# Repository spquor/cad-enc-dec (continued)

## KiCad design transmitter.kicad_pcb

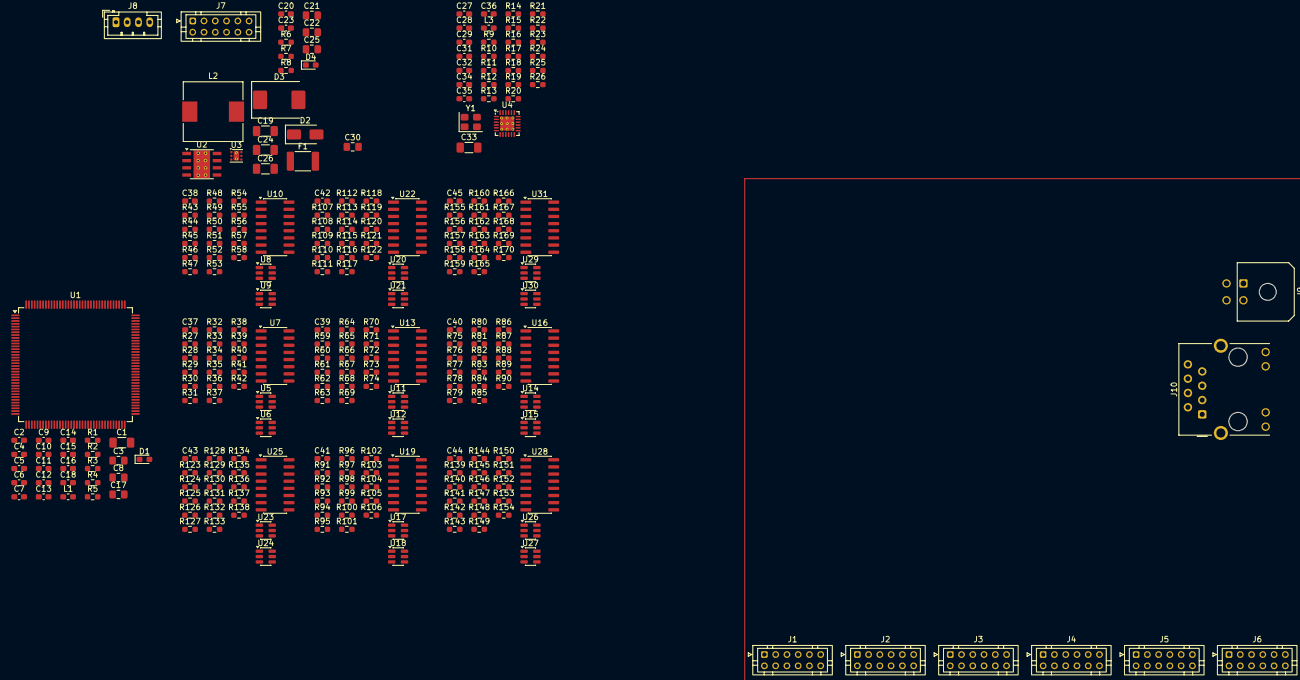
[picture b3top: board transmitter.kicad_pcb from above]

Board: 2 copper layers, 265 parts (0 on the bottom side), 264 nets, no tracks yet.

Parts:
C1, C19, C33: 10uF; C_1206_3216Metric_Pad1.33x1.80mm_HandSolder
C2, C4, C5, C6, C7, C9, C10, C11, C12, C13, C14, C15, C16, C18, C23, C29, C32, C34, C35, C36, C37, C38, C39, C40, C41, C42, C43, C44, C45: 100nF; C_0603_1608Metric_Pad1.08x0.95mm_HandSolder
C3, C8: 2.2uF; C_0805_2012Metric_Pad1.18x1.45mm_HandSolder
C17, C21, C22, C25, C30: 1uF; C_0805_2012Metric_Pad1.18x1.45mm_HandSolder
C20: 220nF; C_0603_1608Metric_Pad1.08x0.95mm_HandSolder
C24, C26: 22uF; C_1206_3216Metric_Pad1.33x1.80mm_HandSolder
C27, C28: 30pF; C_0603_1608Metric_Pad1.08x0.95mm_HandSolder
C31: 470pF; C_0603_1608Metric_Pad1.08x0.95mm_HandSolder
D1, D4: LED Blue; D_0603_1608Metric_Pad1.05x0.95mm_HandSolder
D2: SMAJ28A; D_SMA
D3: SS54; D_SMC
F1: Fuse 24V 3A; Fuse_1812_4532Metric_Pad1.30x3.40mm_HandSolder
J1, J2, J3, J4, J5, J6, J7: JST PHD B12B; JST_PHD_B12B-PHDSS_2x06_P2.00mm_Vertical
J8: JST PH B4B; JST_PH_B4B-PH-K_1x04_P2.00mm_Vertical
J9: Power MX 3.0; Molex_Micro-Fit_3.0_43045-0400_2x02_P3.00mm_Horizontal
J10: HR911105A; RJ45_Hanrun_HR911105A_Horizontal
L1, L3: 600R@100Mhz; L_0603_1608Metric_Pad1.05x0.95mm_HandSolder
L2: 2.2uH; L_10.4x10.4_H4.8
R1, R2, R3, R5, R6, R14, R15, R16, R17, R18, R24: 10K; R_0603_1608Metric_Pad0.98x0.95mm_HandSolder
R4, R39, R40, R41, R42, R55, R56, R57, R58, R71, R72, R73, R74, R87, R88, R89, R90, R103, R104, R105, R106, R119, R120, R121, R122, R135, R136, R137, R138, R151, R152, R153, R154, R167, R168, R169, R170: 0R; R_0603_1608Metric_Pad0.98x0.95mm_HandSolder
R7: 100K; R_0603_1608Metric_Pad0.98x0.95mm_HandSolder
R8: 24K9; R_0603_1608Metric_Pad0.98x0.95mm_HandSolder
R9, R10, R11, R12, R31, R32, R33, R34, R35, R36, R37, R38, R47, R48, R49, R50, R51, R52, R53, R54, R63, R64, R65, R66, R67, R68, R69, R70, R79, R80, R81, R82, R83, R84, R85, R86, R95, R96, R97, R98, R99, R100, R101, R102, R111, R112, R113, R114, R115, R116, R117, R118, R127, R128, R129, R130, R131, R132, R133, R134, R143, R144, R145, R146, R147, R148, R149, R150, R159, R160, R161, R162, R163, R164, R165, R166: 10; R_0603_1608Metric_Pad0.98x0.95mm_HandSolder
R13: 1K5; R_0603_1608Metric_Pad0.98x0.95mm_HandSolder
R19, R20, R21, R23: 49.9; R_0603_1608Metric_Pad0.98x0.95mm_HandSolder
R22: 12K1; R_0603_1608Metric_Pad0.98x0.95mm_HandSolder
R25, R26: 270; R_0603_1608Metric_Pad0.98x0.95mm_HandSolder
R27, R28, R29, R30, R43, R44, R45, R46, R59, R60, R61, R62, R75, R76, R77, R78, R91, R92, R93, R94, R107, R108, R109, R110, R123, R124, R125, R126, R139, R140, R141, R142, R155, R156, R157, R158: 100; R_0603_1608Metric_Pad0.98x0.95mm_HandSolder
U1: STM32H723ZGT; LQFP-144_20x20mm_P0.5mm
U2: LMR33630B; Texas_HSOP-8-1EP_3.9x4.9mm_P1.27mm_ThermalVias
U3: TLV76733; WSON-6-1EP_2x2mm_P0.65mm_EP1x1.6mm_ThermalVias
U4: LAN8742AI; VQFN-24-1EP_4x4mm_P0.5mm_EP2.5x2.5mm_ThermalVias
U5, U6, U8, U9, U11, U12, U14, U15, U17, U18, U20, U21, U23, U24, U26, U27, U29, U30: SRV05-4; SOT-23-6
U7, U10, U13, U16, U19, U22, U25, U28, U31: AM26LV32E; SOIC-16_3.9x9.9mm_P1.27mm
Y1: ABM8G-25MHz; Crystal_SMD_3225-4Pin_3.2x2.5mm

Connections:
+3V3: C1.1, C2.1, C4.1, C5.1, C6.1, C7.1, C9.1, C10.1, C11.1, C12.1, C13.1, C14.1, C15.1, C16.1, C25.1, C29.1, C37.2, C38.2, C39.2, C40.2, C41.2, C42.2, C43.2, C44.2, C45.2, D1.2 (A), J8.1, L1.2, L3.1, R2.1, R3.1, R5.1, R13.2, R14.2, R15.2, R16.2, R17.2, U1.6 (VBAT), U1.17 (VDD), U1.30 (VDD), U1.39 (VDD), U1.52 (VDD), U1.62 (VDD), U1.72 (VDD), U1.84 (VDD), U1.95 (VDD33USB), U1.108 (VDD), U1.121 (VDD), U1.131 (VDD), U1.144 (VDD), U3.1 (OUT), U3.2 (SNS), U4.9 (VDDIO), U7.4 (G), U7.16 (VDD), U10.4 (G), U10.16 (VDD), U13.4 (G), U13.16 (VDD), U16.4 (G), U16.16 (VDD), U19.4 (G), U19.16 (VDD), U22.4 (G), U22.16 (VDD), U25.4 (G), U25.16 (VDD), U28.4 (G), U28.16 (VDD), U31.4 (G), U31.16 (VDD)
+5V: C22.1, C24.1, C26.1, J7.1, J7.3, J7.5, J7.7, J7.9, J7.11, L2.2, R7.2, U3.4 (EN), U3.6 (IN)
+24V: C19.1, C20.1, D3.1 (K), D4.2 (A), F1.2, U2.2 (VIN), U2.3 (EN)
/EN1_A: R39.2, U1.15 (PF5)
/EN1_A1: J1.1, R27.1, R31.1, U5.1 (IO1)
/EN1_A2: J1.2, R27.2, R32.1, U5.3 (IO2)
/EN1_B: R40.2, U1.14 (PF4)
/EN1_B1: J1.3, R28.1, R33.1, U5.4 (IO3)
/EN1_B2: J1.4, R28.2, R34.1, U5.6 (IO4)
/EN1_U: R42.2, U1.12 (PF2)
/EN1_U1: J1.7, R30.1, R37.1, U6.4 (IO3)
/EN1_U2: J1.8, R30.2, R38.1, U6.6 (IO4)
/EN1_V: R55.2, U1.11 (PF1)
/EN1_V1: J1.9, R43.1, R47.1, U8.1 (IO1)
/EN1_V2: J1.10, R43.2, R48.1, U8.3 (IO2)
/EN1_W: R56.2, U1.10 (PF0)
/EN1_W1: J1.11, R44.1, R49.1, U8.4 (IO3)
/EN1_W2: J1.12, R44.2, R50.1, U8.6 (IO4)
/EN1_Z: R41.2, U1.13 (PF3)
/EN1_Z1: J1.5, R29.1, R35.1, U6.1 (IO1)
/EN1_Z2: J1.6, R29.2, R36.1, U6.3 (IO2)
/EN2_A: R57.2, U1.59 (PE8)
/EN2_A1: J2.1, R45.1, R51.1, U9.1 (IO1)
/EN2_A2: J2.2, R45.2, R52.1, U9.3 (IO2)
/EN2_B: R58.2, U1.63 (PE10)
/EN2_B1: J2.3, R46.1, R53.1, U9.4 (IO3)
/EN2_B2: J2.4, R46.2, R54.1, U9.6 (IO4)
/EN2_U: R72.2, U1.66 (PE13)
/EN2_U1: J2.7, R60.1, R65.1, U11.4 (IO3)
/EN2_U2: J2.8, R60.2, R66.1, U11.6 (IO4)
/EN2_V: R73.2, U1.60 (PE9)
/EN2_V1: J2.9, R61.1, R67.1, U12.1 (IO1)
/EN2_V2: J2.10, R61.2, R68.1, U12.3 (IO2)
/EN2_W: R74.2, U1.64 (PE11)
/EN2_W1: J2.11, R62.1, R69.1, U12.4 (IO3)
/EN2_W2: J2.12, R62.2, R70.1, U12.6 (IO4)
/EN2_Z: R71.2, U1.65 (PE12)
/EN2_Z1: J2.5, R59.1, R63.1, U11.1 (IO1)
/EN2_Z2: J2.6, R59.2, R64.1, U11.3 (IO2)
/EN3_A: R87.2, U1.77 (PD8)
/EN3_A1: J3.1, R75.1, R79.1, U14.1 (IO1)
/EN3_A2: J3.2, R75.2, R80.1, U14.3 (IO2)
/EN3_B: R88.2, U1.78 (PD9)
/EN3_B1: J3.3, R76.1, R81.1, U14.4 (IO3)
/EN3_B2: J3.4, R76.2, R82.1, U14.6 (IO4)
/EN3_U: R90.2, U1.80 (PD11)
/EN3_U1: J3.7, R78.1, R85.1, U15.4 (IO3)
/EN3_U2: J3.8, R78.2, R86.1, U15.6 (IO4)
/EN3_V: R103.2, U1.81 (PD12)
/EN3_V1: J3.9, R91.1, R95.1, U17.1 (IO1)
/EN3_V2: J3.10, R91.2, R96.1, U17.3 (IO2)
/EN3_W: R104.2, U1.82 (PD13)
/EN3_W1: J3.11, R92.1, R97.1, U17.4 (IO3)
/EN3_W2: J3.12, R92.2, R98.1, U17.6 (IO4)
/EN3_Z: R89.2, U1.79 (PD10)
/EN3_Z1: J3.5, R77.1, R83.1, U15.1 (IO1)
/EN3_Z2: J3.6, R77.2, R84.1, U15.3 (IO2)
/EN4_A: R105.2, U1.90 (PG5)
/EN4_A1: J4.1, R93.1, R99.1, U18.1 (IO1)
/EN4_A2: J4.2, R93.2, R100.1, U18.3 (IO2)
/EN4_B: R106.2, U1.91 (PG6)
/EN4_B1: J4.3, R94.1, R101.1, U18.4 (IO3)
/EN4_B2: J4.4, R94.2, R102.1, U18.6 (IO4)
/EN4_U: R120.2, U1.93 (PG8)
/EN4_U1: J4.7, R108.1, R113.1, U20.4 (IO3)
/EN4_U2: J4.8, R108.2, R114.1, U20.6 (IO4)
/EN4_V: R121.2, U1.96 (PC6)
/EN4_V1: J4.9, R109.1, R115.1, U21.1 (IO1)
/EN4_V2: J4.10, R109.2, R116.1, U21.3 (IO2)
/EN4_W: R122.2, U1.97 (PC7)
/EN4_W1: J4.11, R110.1, R117.1, U21.4 (IO3)
/EN4_W2: J4.12, R110.2, R118.1, U21.6 (IO4)
/EN4_Z: R119.2, U1.92 (PG7)
/EN4_Z1: J4.5, R107.1, R111.1, U20.1 (IO1)
/EN4_Z2: J4.6, R107.2, R112.1, U20.3 (IO2)
/EN5_A: R135.2, U1.111 (PC10)
/EN5_A1: J5.1, R123.1, R127.1, U23.1 (IO1)
/EN5_A2: J5.2, R123.2, R128.1, U23.3 (IO2)
/EN5_B: R136.2, U1.112 (PC11)
/EN5_B1: J5.3, R124.1, R129.1, U23.4 (IO3)
/EN5_B2: J5.4, R124.2, R130.1, U23.6 (IO4)
/EN5_U: R138.2, U1.115 (PD1)
/EN5_U1: J5.7, R126.1, R133.1, U24.4 (IO3)
/EN5_U2: J5.8, R126.2, R134.1, U24.6 (IO4)
/EN5_V: R151.2, U1.110 (PA15(JTDI))
/EN5_V1: J5.9, R139.1, R143.1, U26.1 (IO1)
/EN5_V2: J5.10, R139.2, R144.1, U26.3 (IO2)
/EN5_W: R152.2, U1.133 (PB3(JTDO)
/EN5_W1: J5.11, R140.1, R145.1, U26.4 (IO3)
/EN5_W2: J5.12, R140.2, R146.1, U26.6 (IO4)
/EN5_Z: R137.2, U1.114 (PD0)
/EN5_Z1: J5.5, R125.1, R131.1, U24.1 (IO1)
/EN5_Z2: J5.6, R125.2, R132.1, U24.3 (IO2)
/EN6_A: R153.2, U1.125 (PG10)
/EN6_A1: J6.1, R141.1, R147.1, U27.1 (IO1)
/EN6_A2: J6.2, R141.2, R148.1, U27.3 (IO2)
/EN6_B: R154.2, U1.126 (PG11)
/EN6_B1: J6.3, R142.1, R149.1, U27.4 (IO3)
/EN6_B2: J6.4, R142.2, R150.1, U27.6 (IO4)
/EN6_U: R168.2, U1.128 (PG13)
/EN6_U1: J6.7, R156.1, R161.1, U29.4 (IO3)
/EN6_U2: J6.8, R156.2, R162.1, U29.6 (IO4)
/EN6_V: R169.2, U1.134 (PB4(NJTRST))
/EN6_V1: J6.9, R157.1, R163.1, U30.1 (IO1)
/EN6_V2: J6.10, R157.2, R164.1, U30.3 (IO2)
/EN6_W: R170.2, U1.135 (PB5)
/EN6_W1: J6.11, R158.1, R165.1, U30.4 (IO3)
/EN6_W2: J6.12, R158.2, R166.1, U30.6 (IO4)
/EN6_Z: R167.2, U1.127 (PG12)
/EN6_Z1: J6.5, R155.1, R159.1, U29.1 (IO1)
/EN6_Z2: J6.6, R155.2, R160.1, U29.3 (IO2)
/Ethernet/CRS: R11.1, U1.43 (PA7)
/Ethernet/MDC: R16.1, U1.27 (PC1), U4.13 (MDC)
/Ethernet/MDIO: R13.1, U1.36 (PA2), U4.12 (MDIO)
/Ethernet/REFCLK: R12.1, U1.35 (PA1)
/Ethernet/RXD0: R9.1, U1.44 (PC4)
/Ethernet/RXD1: R10.1, U1.45 (PC5)
/Ethernet/TXD0: U1.73 (PB12), U4.17 (TXD0)
/Ethernet/TXD1: U1.74 (PB13), U4.18 (TXD1)
/Ethernet/TXEN: U1.70 (PB11), U4.16 (TXEN)
/Ethernet/nRST: U1.69 (PB10), U4.15 (~RST)
/SWDCLK: J8.2, U1.109 (PA14(JTCK)
/SWDIO: J8.3, U1.105 (PA13(JTMS)
GND: C1.2, C2.2, C3.2, C4.2, C5.2, C6.2, C7.2, C8.2, C9.2, C10.2, C11.2, C12.2, C13.2, C14.2, C15.2, C16.2, C17.2, C18.2, C19.2, C20.2, C21.2, C22.2, C24.2, C25.2, C26.2, C27.1, C28.1, C29.2, C30.2, C31.2, C32.2, C33.2, C34.2, C35.2, C36.2, C37.1, C38.1, C39.1, C40.1, C41.1, C42.1, C43.1, C44.1, C45.1, D2.2 (A2), D3.2 (A), J7.2, J7.4, J7.6, J7.8, J7.10, J7.12, J8.4, J9.3, J9.4, J10.8, J10.SH, R1.1, R6.1, R8.1, R18.1, R22.1, R24.1, R25.1, R26.1, U1.16 (VSS), U1.31 (VSSA), U1.38 (VSS), U1.51 (VSS), U1.61 (VSS), U1.83 (VSS), U1.94 (VSS), U1.107 (VSS), U1.120 (VSS), U1.130 (VSS), U2.1 (GND), U2.9 (GND), U3.3 (GND), U3.5 (GND), U3.7 (PAD), U4.25 (VSS), U5.2 (VN), U6.2 (VN), U7.8 (GND), U7.12 (~G), U8.2 (VN), U9.2 (VN), U10.8 (GND), U10.12 (~G), U11.2 (VN), U12.2 (VN), U13.8 (GND), U13.12 (~G), U14.2 (VN), U15.2 (VN), U16.8 (GND), U16.12 (~G), U17.2 (VN), U18.2 (VN), U19.8 (GND), U19.12 (~G), U20.2 (VN), U21.2 (VN), U22.8 (GND), U22.12 (~G), U23.2 (VN), U24.2 (VN), U25.8 (GND), U25.12 (~G), U26.2 (VN), U27.2 (VN), U28.8 (GND), U28.12 (~G), U29.2 (VN), U30.2 (VN), U31.8 (GND), U31.12 (~G), Y1.2 (G), Y1.4 (G)
unnamed: C3.1, U1.71 (VCAP)
unnamed: C8.1, U1.106 (VCAP)
unnamed: D1.1 (K), R1.2
unnamed: D4.1 (K), R6.2
unnamed: J10.10, R25.2
unnamed: J10.11, R26.2
unnamed: C32.1, C33.1, C34.1, C35.1, C36.1, J10.4 (TCT), J10.5 (RCT), L3.2, R19.2, R20.2, R21.2, R23.2, U4.1 (VDD2A), U4.19 (VDD1A)
unnamed: J10.3 (RD+), R21.1, U4.23 (RXP)
unnamed: J10.6 (RD-), R23.1, U4.22 (RXN)
unnamed: J10.1 (TD+), R19.1, U4.21 (TXP)
unnamed: J10.2 (TD-), R20.1, U4.20 (TXN)
unnamed: R3.2, U1.138 (BOOT0)
unnamed: R2.2, U1.25 (NRST)
unnamed: R5.2, U1.143 (PDR_ON)
unnamed: C17.1, C18.1, L1.1, U1.33 (VDDA)
unnamed: R4.2, U1.32 (VREF+)
unnamed: C23.1, U2.7 (BOOT)
unnamed: R7.1, R8.2, U2.5 (FB)
unnamed: C23.2, L2.1, U2.8 (SW)
unnamed: C21.1, U2.6 (VCC)
unnamed: R11.2, U4.11 (CRS_DV/MODE2)
unnamed: J10.12, U4.3 (LED1/REGOFF)
unnamed: J10.9, R24.2, U4.2 (LED2/~INTSEL)
unnamed: R22.2, U4.24 (RBIAS)
unnamed: R9.2, R14.1, U4.8 (RXD0/MODE0)
unnamed: R10.2, R15.1, U4.7 (RXD1/MODE1)
unnamed: R18.2, U4.10 (RXER/PHYAD0)
unnamed: C30.1, C31.1, U4.6 (VDDCR)
unnamed: C27.2, U4.5 (XTAL1/CLKIN), Y1.3
unnamed: C28.2, U4.4 (XTAL2), Y1.1
unnamed: R12.2, R17.1, U4.14 (~INT/REFCLKO)
unnamed: R31.2, U7.2 (1A)
unnamed: R32.2, U7.1 (1B)
unnamed: R39.1, U7.3 (1Y)
unnamed: R33.2, U7.6 (2A)
unnamed: R34.2, U7.7 (2B)
unnamed: R40.1, U7.5 (2Y)
unnamed: R35.2, U7.10 (3A)
unnamed: R36.2, U7.9 (3B)
unnamed: R41.1, U7.11 (3Y)
unnamed: R37.2, U7.14 (4A)
unnamed: R38.2, U7.15 (4B)
unnamed: R42.1, U7.13 (4Y)
unnamed: R47.2, U10.2 (1A)
unnamed: R48.2, U10.1 (1B)
unnamed: R55.1, U10.3 (1Y)
unnamed: R49.2, U10.6 (2A)
unnamed: R50.2, U10.7 (2B)
unnamed: R56.1, U10.5 (2Y)
unnamed: R51.2, U10.10 (3A)
unnamed: R52.2, U10.9 (3B)
unnamed: R57.1, U10.11 (3Y)
unnamed: R53.2, U10.14 (4A)
unnamed: R54.2, U10.15 (4B)
unnamed: R58.1, U10.13 (4Y)
unnamed: R63.2, U13.2 (1A)
unnamed: R64.2, U13.1 (1B)
unnamed: R71.1, U13.3 (1Y)
unnamed: R65.2, U13.6 (2A)
unnamed: R66.2, U13.7 (2B)
unnamed: R72.1, U13.5 (2Y)
unnamed: R67.2, U13.10 (3A)
unnamed: R68.2, U13.9 (3B)
unnamed: R73.1, U13.11 (3Y)
unnamed: R69.2, U13.14 (4A)
unnamed: R70.2, U13.15 (4B)
unnamed: R74.1, U13.13 (4Y)
unnamed: R79.2, U16.2 (1A)
unnamed: R80.2, U16.1 (1B)
unnamed: R87.1, U16.3 (1Y)
unnamed: R81.2, U16.6 (2A)
unnamed: R82.2, U16.7 (2B)
unnamed: R88.1, U16.5 (2Y)
unnamed: R83.2, U16.10 (3A)
unnamed: R84.2, U16.9 (3B)
unnamed: R89.1, U16.11 (3Y)
unnamed: R85.2, U16.14 (4A)
unnamed: R86.2, U16.15 (4B)
unnamed: R90.1, U16.13 (4Y)
unnamed: R95.2, U19.2 (1A)
unnamed: R96.2, U19.1 (1B)
unnamed: R103.1, U19.3 (1Y)
unnamed: R97.2, U19.6 (2A)
unnamed: R98.2, U19.7 (2B)
unnamed: R104.1, U19.5 (2Y)
unnamed: R99.2, U19.10 (3A)
unnamed: R100.2, U19.9 (3B)
unnamed: R105.1, U19.11 (3Y)
unnamed: R101.2, U19.14 (4A)
unnamed: R102.2, U19.15 (4B)
unnamed: R106.1, U19.13 (4Y)
unnamed: R111.2, U22.2 (1A)
unnamed: R112.2, U22.1 (1B)
unnamed: R119.1, U22.3 (1Y)
unnamed: R113.2, U22.6 (2A)
unnamed: R114.2, U22.7 (2B)
unnamed: R120.1, U22.5 (2Y)
unnamed: R115.2, U22.10 (3A)
unnamed: R116.2, U22.9 (3B)
unnamed: R121.1, U22.11 (3Y)
unnamed: R117.2, U22.14 (4A)
unnamed: R118.2, U22.15 (4B)
unnamed: R122.1, U22.13 (4Y)
unnamed: R127.2, U25.2 (1A)
unnamed: R128.2, U25.1 (1B)
unnamed: R135.1, U25.3 (1Y)
unnamed: R129.2, U25.6 (2A)
unnamed: R130.2, U25.7 (2B)
unnamed: R136.1, U25.5 (2Y)
unnamed: R131.2, U25.10 (3A)
unnamed: R132.2, U25.9 (3B)
unnamed: R137.1, U25.11 (3Y)
unnamed: R133.2, U25.14 (4A)
unnamed: R134.2, U25.15 (4B)
unnamed: R138.1, U25.13 (4Y)
unnamed: R143.2, U28.2 (1A)
unnamed: R144.2, U28.1 (1B)
unnamed: R151.1, U28.3 (1Y)
unnamed: R145.2, U28.6 (2A)
unnamed: R146.2, U28.7 (2B)
unnamed: R152.1, U28.5 (2Y)
unnamed: R147.2, U28.10 (3A)
unnamed: R148.2, U28.9 (3B)
unnamed: R153.1, U28.11 (3Y)
unnamed: R149.2, U28.14 (4A)
unnamed: R150.2, U28.15 (4B)
unnamed: R154.1, U28.13 (4Y)
unnamed: R159.2, U31.2 (1A)
unnamed: R160.2, U31.1 (1B)
unnamed: R167.1, U31.3 (1Y)
unnamed: R161.2, U31.6 (2A)
unnamed: R162.2, U31.7 (2B)
unnamed: R168.1, U31.5 (2Y)
unnamed: R163.2, U31.10 (3A)
unnamed: R164.2, U31.9 (3B)
unnamed: R169.1, U31.11 (3Y)
unnamed: R165.2, U31.14 (4A)
unnamed: R166.2, U31.15 (4B)
unnamed: R170.1, U31.13 (4Y)
VDD: D2.1 (A1), F1.1, J9.1, J9.2

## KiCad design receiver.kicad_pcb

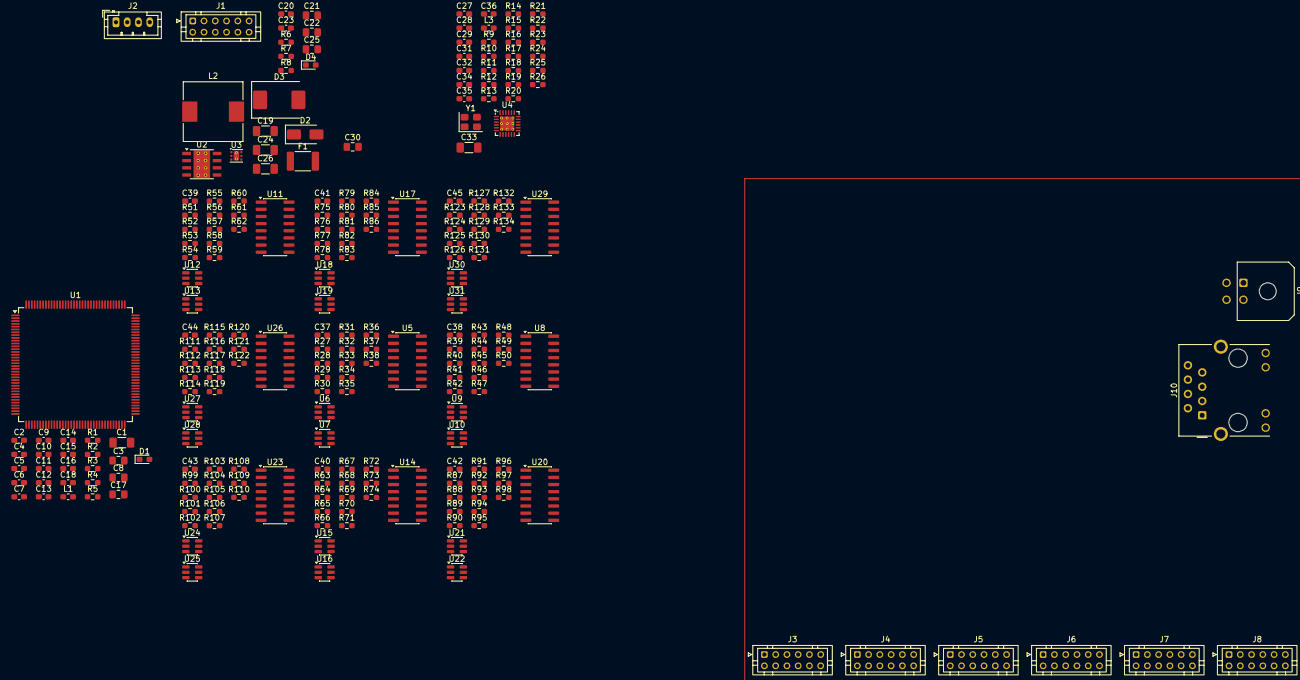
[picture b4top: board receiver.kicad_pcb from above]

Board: 2 copper layers, 229 parts (0 on the bottom side), 264 nets, no tracks yet.

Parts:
C1, C19, C33: 10uF; C_1206_3216Metric_Pad1.33x1.80mm_HandSolder
C2, C4, C5, C6, C7, C9, C10, C11, C12, C13, C14, C15, C16, C18, C23, C29, C32, C34, C35, C36, C37, C38, C39, C40, C41, C42, C43, C44, C45: 100nF; C_0603_1608Metric_Pad1.08x0.95mm_HandSolder
C3, C8: 2.2uF; C_0805_2012Metric_Pad1.18x1.45mm_HandSolder
C17, C21, C22, C25, C30: 1uF; C_0805_2012Metric_Pad1.18x1.45mm_HandSolder
C20: 220nF; C_0603_1608Metric_Pad1.08x0.95mm_HandSolder
C24, C26: 22uF; C_1206_3216Metric_Pad1.33x1.80mm_HandSolder
C27, C28: 30pF; C_0603_1608Metric_Pad1.08x0.95mm_HandSolder
C31: 470pF; C_0603_1608Metric_Pad1.08x0.95mm_HandSolder
D1, D4: LED Blue; D_0603_1608Metric_Pad1.05x0.95mm_HandSolder
D2: SMAJ28A; D_SMA
D3: SS54; D_SMC
F1: Fuse 24V 3A; Fuse_1812_4532Metric_Pad1.30x3.40mm_HandSolder
J1, J3, J4, J5, J6, J7, J8: JST PHD B12B; JST_PHD_B12B-PHDSS_2x06_P2.00mm_Vertical
J2: JST PH B4B; JST_PH_B4B-PH-K_1x04_P2.00mm_Vertical
J9: Power MX 3.0; Molex_Micro-Fit_3.0_43045-0400_2x02_P3.00mm_Horizontal
J10: HR911105A; RJ45_Hanrun_HR911105A_Horizontal
L1, L3: 600R@100Mhz; L_0603_1608Metric_Pad1.05x0.95mm_HandSolder
L2: 2.2uH; L_10.4x10.4_H4.8
R1, R2, R3, R5, R6, R14, R15, R16, R17, R18, R24: 10K; R_0603_1608Metric_Pad0.98x0.95mm_HandSolder
R4, R27, R28, R29, R30, R39, R40, R41, R42, R51, R52, R53, R54, R63, R64, R65, R66, R75, R76, R77, R78, R87, R88, R89, R90, R99, R100, R101, R102, R111, R112, R113, R114, R123, R124, R125, R126: 0R; R_0603_1608Metric_Pad0.98x0.95mm_HandSolder
R7: 100K; R_0603_1608Metric_Pad0.98x0.95mm_HandSolder
R8: 24K9; R_0603_1608Metric_Pad0.98x0.95mm_HandSolder
R9, R10, R11, R12, R31, R32, R33, R34, R35, R36, R37, R38, R43, R44, R45, R46, R47, R48, R49, R50, R55, R56, R57, R58, R59, R60, R61, R62, R67, R68, R69, R70, R71, R72, R73, R74, R79, R80, R81, R82, R83, R84, R85, R86, R91, R92, R93, R94, R95, R96, R97, R98, R103, R104, R105, R106, R107, R108, R109, R110, R115, R116, R117, R118, R119, R120, R121, R122, R127, R128, R129, R130, R131, R132, R133, R134: 10; R_0603_1608Metric_Pad0.98x0.95mm_HandSolder
R13: 1K5; R_0603_1608Metric_Pad0.98x0.95mm_HandSolder
R19, R20, R21, R23: 49.9; R_0603_1608Metric_Pad0.98x0.95mm_HandSolder
R22: 12K1; R_0603_1608Metric_Pad0.98x0.95mm_HandSolder
R25, R26: 270; R_0603_1608Metric_Pad0.98x0.95mm_HandSolder
U1: STM32H723ZGT; LQFP-144_20x20mm_P0.5mm
U2: LMR33630B; Texas_HSOP-8-1EP_3.9x4.9mm_P1.27mm_ThermalVias
U3: TLV76733; WSON-6-1EP_2x2mm_P0.65mm_EP1x1.6mm_ThermalVias
U4: LAN8742AI; VQFN-24-1EP_4x4mm_P0.5mm_EP2.5x2.5mm_ThermalVias
U5, U8, U11, U14, U17, U20, U23, U26, U29: AM26LV31E; SOIC-16_3.9x9.9mm_P1.27mm
U6, U7, U9, U10, U12, U13, U15, U16, U18, U19, U21, U22, U24, U25, U27, U28, U30, U31: SRV05-4; SOT-23-6
Y1: ABM8G-25MHz; Crystal_SMD_3225-4Pin_3.2x2.5mm

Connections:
+3V3: C1.1, C2.1, C4.1, C5.1, C6.1, C7.1, C9.1, C10.1, C11.1, C12.1, C13.1, C14.1, C15.1, C16.1, C25.1, C29.1, C37.2, C38.2, C39.2, C40.2, C41.2, C42.2, C43.2, C44.2, C45.2, D1.2 (A), J2.1, L1.2, L3.1, R2.1, R3.1, R5.1, R13.2, R14.2, R15.2, R16.2, R17.2, U1.6 (VBAT), U1.17 (VDD), U1.30 (VDD), U1.39 (VDD), U1.52 (VDD), U1.62 (VDD), U1.72 (VDD), U1.84 (VDD), U1.95 (VDD33USB), U1.108 (VDD), U1.121 (VDD), U1.131 (VDD), U1.144 (VDD), U3.1 (OUT), U3.2 (SNS), U4.9 (VDDIO), U5.4 (G), U5.16 (VDD), U8.4 (G), U8.16 (VDD), U11.4 (G), U11.16 (VDD), U14.4 (G), U14.16 (VDD), U17.4 (G), U17.16 (VDD), U20.4 (G), U20.16 (VDD), U23.4 (G), U23.16 (VDD), U26.4 (G), U26.16 (VDD), U29.4 (G), U29.16 (VDD)
+5V: C22.1, C24.1, C26.1, J1.1, J1.3, J1.5, J1.7, J1.9, J1.11, L2.2, R7.2, U3.4 (EN), U3.6 (IN)
+24V: C19.1, C20.1, D3.1 (K), D4.2 (A), F1.2, U2.2 (VIN), U2.3 (EN)
/EN1_A: R27.1, U1.15 (PF5)
/EN1_A1: J3.1, R31.2, U6.1 (IO1)
/EN1_A2: J3.2, R32.2, U6.3 (IO2)
/EN1_B: R28.1, U1.14 (PF4)
/EN1_B1: J3.3, R33.2, U6.4 (IO3)
/EN1_B2: J3.4, R34.2, U6.6 (IO4)
/EN1_U: R30.1, U1.12 (PF2)
/EN1_U1: J3.7, R37.2, U7.4 (IO3)
/EN1_U2: J3.8, R38.2, U7.6 (IO4)
/EN1_V: R39.1, U1.11 (PF1)
/EN1_V1: J3.9, R43.2, U9.1 (IO1)
/EN1_V2: J3.10, R44.2, U9.3 (IO2)
/EN1_W: R40.1, U1.10 (PF0)
/EN1_W1: J3.11, R45.2, U9.4 (IO3)
/EN1_W2: J3.12, R46.2, U9.6 (IO4)
/EN1_Z: R29.1, U1.13 (PF3)
/EN1_Z1: J3.5, R35.2, U7.1 (IO1)
/EN1_Z2: J3.6, R36.2, U7.3 (IO2)
/EN2_A: R41.1, U1.59 (PE8)
/EN2_A1: J4.1, R47.2, U10.1 (IO1)
/EN2_A2: J4.2, R48.2, U10.3 (IO2)
/EN2_B: R42.1, U1.63 (PE10)
/EN2_B1: J4.3, R49.2, U10.4 (IO3)
/EN2_B2: J4.4, R50.2, U10.6 (IO4)
/EN2_U: R52.1, U1.66 (PE13)
/EN2_U1: J4.7, R57.2, U12.4 (IO3)
/EN2_U2: J4.8, R58.2, U12.6 (IO4)
/EN2_V: R53.1, U1.60 (PE9)
/EN2_V1: J4.9, R59.2, U13.1 (IO1)
/EN2_V2: J4.10, R60.2, U13.3 (IO2)
/EN2_W: R54.1, U1.64 (PE11)
/EN2_W1: J4.11, R61.2, U13.4 (IO3)
/EN2_W2: J4.12, R62.2, U13.6 (IO4)
/EN2_Z: R51.1, U1.65 (PE12)
/EN2_Z1: J4.5, R55.2, U12.1 (IO1)
/EN2_Z2: J4.6, R56.2, U12.3 (IO2)
/EN3_A: R63.1, U1.77 (PD8)
/EN3_A1: J5.1, R67.2, U15.1 (IO1)
/EN3_A2: J5.2, R68.2, U15.3 (IO2)
/EN3_B: R64.1, U1.78 (PD9)
/EN3_B1: J5.3, R69.2, U15.4 (IO3)
/EN3_B2: J5.4, R70.2, U15.6 (IO4)
/EN3_U: R66.1, U1.80 (PD11)
/EN3_U1: J5.7, R73.2, U16.4 (IO3)
/EN3_U2: J5.8, R74.2, U16.6 (IO4)
/EN3_V: R75.1, U1.81 (PD12)
/EN3_V1: J5.9, R79.2, U18.1 (IO1)
/EN3_V2: J5.10, R80.2, U18.3 (IO2)
/EN3_W: R76.1, U1.82 (PD13)
/EN3_W1: J5.11, R81.2, U18.4 (IO3)
/EN3_W2: J5.12, R82.2, U18.6 (IO4)
/EN3_Z: R65.1, U1.79 (PD10)
/EN3_Z1: J5.5, R71.2, U16.1 (IO1)
/EN3_Z2: J5.6, R72.2, U16.3 (IO2)
/EN4_A: R77.1, U1.90 (PG5)
/EN4_A1: J6.1, R83.2, U19.1 (IO1)
/EN4_A2: J6.2, R84.2, U19.3 (IO2)
/EN4_B: R78.1, U1.91 (PG6)
/EN4_B1: J6.3, R85.2, U19.4 (IO3)
/EN4_B2: J6.4, R86.2, U19.6 (IO4)
/EN4_U: R88.1, U1.93 (PG8)
/EN4_U1: J6.7, R93.2, U21.4 (IO3)
/EN4_U2: J6.8, R94.2, U21.6 (IO4)
/EN4_V: R89.1, U1.96 (PC6)
/EN4_V1: J6.9, R95.2, U22.1 (IO1)
/EN4_V2: J6.10, R96.2, U22.3 (IO2)
/EN4_W: R90.1, U1.97 (PC7)
/EN4_W1: J6.11, R97.2, U22.4 (IO3)
/EN4_W2: J6.12, R98.2, U22.6 (IO4)
/EN4_Z: R87.1, U1.92 (PG7)
/EN4_Z1: J6.5, R91.2, U21.1 (IO1)
/EN4_Z2: J6.6, R92.2, U21.3 (IO2)
/EN5_A: R99.1, U1.111 (PC10)
/EN5_A1: J7.1, R103.2, U24.1 (IO1)
/EN5_A2: J7.2, R104.2, U24.3 (IO2)
/EN5_B: R100.1, U1.112 (PC11)
/EN5_B1: J7.3, R105.2, U24.4 (IO3)
/EN5_B2: J7.4, R106.2, U24.6 (IO4)
/EN5_U: R102.1, U1.115 (PD1)
/EN5_U1: J7.7, R109.2, U25.4 (IO3)
/EN5_U2: J7.8, R110.2, U25.6 (IO4)
/EN5_V: R111.1, U1.110 (PA15(JTDI))
/EN5_V1: J7.9, R115.2, U27.1 (IO1)
/EN5_V2: J7.10, R116.2, U27.3 (IO2)
/EN5_W: R112.1, U1.133 (PB3(JTDO)
/EN5_W1: J7.11, R117.2, U27.4 (IO3)
/EN5_W2: J7.12, R118.2, U27.6 (IO4)
/EN5_Z: R101.1, U1.114 (PD0)
/EN5_Z1: J7.5, R107.2, U25.1 (IO1)
/EN5_Z2: J7.6, R108.2, U25.3 (IO2)
/EN6_A: R113.1, U1.125 (PG10)
/EN6_A1: J8.1, R119.2, U28.1 (IO1)
/EN6_A2: J8.2, R120.2, U28.3 (IO2)
/EN6_B: R114.1, U1.126 (PG11)
/EN6_B1: J8.3, R121.2, U28.4 (IO3)
/EN6_B2: J8.4, R122.2, U28.6 (IO4)
/EN6_U: R124.1, U1.128 (PG13)
/EN6_U1: J8.7, R129.2, U30.4 (IO3)
/EN6_U2: J8.8, R130.2, U30.6 (IO4)
/EN6_V: R125.1, U1.134 (PB4(NJTRST))
/EN6_V1: J8.9, R131.2, U31.1 (IO1)
/EN6_V2: J8.10, R132.2, U31.3 (IO2)
/EN6_W: R126.1, U1.135 (PB5)
/EN6_W1: J8.11, R133.2, U31.4 (IO3)
/EN6_W2: J8.12, R134.2, U31.6 (IO4)
/EN6_Z: R123.1, U1.127 (PG12)
/EN6_Z1: J8.5, R127.2, U30.1 (IO1)
/EN6_Z2: J8.6, R128.2, U30.3 (IO2)
/Ethernet/CRS: R11.1, U1.43 (PA7)
/Ethernet/MDC: R16.1, U1.27 (PC1), U4.13 (MDC)
/Ethernet/MDIO: R13.1, U1.36 (PA2), U4.12 (MDIO)
/Ethernet/REFCLK: R12.1, U1.35 (PA1)
/Ethernet/RXD0: R9.1, U1.44 (PC4)
/Ethernet/RXD1: R10.1, U1.45 (PC5)
/Ethernet/TXD0: U1.73 (PB12), U4.17 (TXD0)
/Ethernet/TXD1: U1.74 (PB13), U4.18 (TXD1)
/Ethernet/TXEN: U1.70 (PB11), U4.16 (TXEN)
/Ethernet/nRST: U1.69 (PB10), U4.15 (~RST)
/SWDCLK: J2.2, U1.109 (PA14(JTCK)
/SWDIO: J2.3, U1.105 (PA13(JTMS)
GND: C1.2, C2.2, C3.2, C4.2, C5.2, C6.2, C7.2, C8.2, C9.2, C10.2, C11.2, C12.2, C13.2, C14.2, C15.2, C16.2, C17.2, C18.2, C19.2, C20.2, C21.2, C22.2, C24.2, C25.2, C26.2, C27.1, C28.1, C29.2, C30.2, C31.2, C32.2, C33.2, C34.2, C35.2, C36.2, C37.1, C38.1, C39.1, C40.1, C41.1, C42.1, C43.1, C44.1, C45.1, D2.2 (A2), D3.2 (A), J1.2, J1.4, J1.6, J1.8, J1.10, J1.12, J2.4, J9.3, J9.4, J10.8, J10.SH, R1.1, R6.1, R8.1, R18.1, R22.1, R24.1, R25.1, R26.1, U1.16 (VSS), U1.31 (VSSA), U1.38 (VSS), U1.51 (VSS), U1.61 (VSS), U1.83 (VSS), U1.94 (VSS), U1.107 (VSS), U1.120 (VSS), U1.130 (VSS), U2.1 (GND), U2.9 (GND), U3.3 (GND), U3.5 (GND), U3.7 (PAD), U4.25 (VSS), U5.8 (GND), U5.12 (~G), U6.2 (VN), U7.2 (VN), U8.8 (GND), U8.12 (~G), U9.2 (VN), U10.2 (VN), U11.8 (GND), U11.12 (~G), U12.2 (VN), U13.2 (VN), U14.8 (GND), U14.12 (~G), U15.2 (VN), U16.2 (VN), U17.8 (GND), U17.12 (~G), U18.2 (VN), U19.2 (VN), U20.8 (GND), U20.12 (~G), U21.2 (VN), U22.2 (VN), U23.8 (GND), U23.12 (~G), U24.2 (VN), U25.2 (VN), U26.8 (GND), U26.12 (~G), U27.2 (VN), U28.2 (VN), U29.8 (GND), U29.12 (~G), U30.2 (VN), U31.2 (VN), Y1.2 (G), Y1.4 (G)
unnamed: C3.1, U1.71 (VCAP)
unnamed: C8.1, U1.106 (VCAP)
unnamed: D1.1 (K), R1.2
unnamed: D4.1 (K), R6.2
unnamed: J10.10, R25.2
unnamed: J10.11, R26.2
unnamed: C32.1, C33.1, C34.1, C35.1, C36.1, J10.4 (TCT), J10.5 (RCT), L3.2, R19.2, R20.2, R21.2, R23.2, U4.1 (VDD2A), U4.19 (VDD1A)
unnamed: J10.3 (RD+), R21.1, U4.23 (RXP)
unnamed: J10.6 (RD-), R23.1, U4.22 (RXN)
unnamed: J10.1 (TD+), R19.1, U4.21 (TXP)
unnamed: J10.2 (TD-), R20.1, U4.20 (TXN)
unnamed: R3.2, U1.138 (BOOT0)
unnamed: R2.2, U1.25 (NRST)
unnamed: R5.2, U1.143 (PDR_ON)
unnamed: C17.1, C18.1, L1.1, U1.33 (VDDA)
unnamed: R4.2, U1.32 (VREF+)
unnamed: C23.1, U2.7 (BOOT)
unnamed: R7.1, R8.2, U2.5 (FB)
unnamed: C23.2, L2.1, U2.8 (SW)
unnamed: C21.1, U2.6 (VCC)
unnamed: R11.2, U4.11 (CRS_DV/MODE2)
unnamed: J10.12, U4.3 (LED1/REGOFF)
unnamed: J10.9, R24.2, U4.2 (LED2/~INTSEL)
unnamed: R22.2, U4.24 (RBIAS)
unnamed: R9.2, R14.1, U4.8 (RXD0/MODE0)
unnamed: R10.2, R15.1, U4.7 (RXD1/MODE1)
unnamed: R18.2, U4.10 (RXER/PHYAD0)
unnamed: C30.1, C31.1, U4.6 (VDDCR)
unnamed: C27.2, U4.5 (XTAL1/CLKIN), Y1.3
unnamed: C28.2, U4.4 (XTAL2), Y1.1
unnamed: R12.2, R17.1, U4.14 (~INT/REFCLKO)
unnamed: R27.2, U5.1 (1A)
unnamed: R31.1, U5.2 (1Y)
unnamed: R32.1, U5.3 (1Z)
unnamed: R28.2, U5.7 (2A)
unnamed: R33.1, U5.6 (2Y)
unnamed: R34.1, U5.5 (2Z)
unnamed: R29.2, U5.9 (3A)
unnamed: R35.1, U5.10 (3Y)
unnamed: R36.1, U5.11 (3Z)
unnamed: R30.2, U5.15 (4A)
unnamed: R37.1, U5.14 (4Y)
unnamed: R38.1, U5.13 (4Z)
unnamed: R39.2, U8.1 (1A)
unnamed: R43.1, U8.2 (1Y)
unnamed: R44.1, U8.3 (1Z)
unnamed: R40.2, U8.7 (2A)
unnamed: R45.1, U8.6 (2Y)
unnamed: R46.1, U8.5 (2Z)
unnamed: R41.2, U8.9 (3A)
unnamed: R47.1, U8.10 (3Y)
unnamed: R48.1, U8.11 (3Z)
unnamed: R42.2, U8.15 (4A)
unnamed: R49.1, U8.14 (4Y)
unnamed: R50.1, U8.13 (4Z)
unnamed: R51.2, U11.1 (1A)
unnamed: R55.1, U11.2 (1Y)
unnamed: R56.1, U11.3 (1Z)
unnamed: R52.2, U11.7 (2A)
unnamed: R57.1, U11.6 (2Y)
unnamed: R58.1, U11.5 (2Z)
unnamed: R53.2, U11.9 (3A)
unnamed: R59.1, U11.10 (3Y)
unnamed: R60.1, U11.11 (3Z)
unnamed: R54.2, U11.15 (4A)
unnamed: R61.1, U11.14 (4Y)
unnamed: R62.1, U11.13 (4Z)
unnamed: R63.2, U14.1 (1A)
unnamed: R67.1, U14.2 (1Y)
unnamed: R68.1, U14.3 (1Z)
unnamed: R64.2, U14.7 (2A)
unnamed: R69.1, U14.6 (2Y)
unnamed: R70.1, U14.5 (2Z)
unnamed: R65.2, U14.9 (3A)
unnamed: R71.1, U14.10 (3Y)
unnamed: R72.1, U14.11 (3Z)
unnamed: R66.2, U14.15 (4A)
unnamed: R73.1, U14.14 (4Y)
unnamed: R74.1, U14.13 (4Z)
unnamed: R75.2, U17.1 (1A)
unnamed: R79.1, U17.2 (1Y)
unnamed: R80.1, U17.3 (1Z)
unnamed: R76.2, U17.7 (2A)
unnamed: R81.1, U17.6 (2Y)
unnamed: R82.1, U17.5 (2Z)
unnamed: R77.2, U17.9 (3A)
unnamed: R83.1, U17.10 (3Y)
unnamed: R84.1, U17.11 (3Z)
unnamed: R78.2, U17.15 (4A)
unnamed: R85.1, U17.14 (4Y)
unnamed: R86.1, U17.13 (4Z)
unnamed: R87.2, U20.1 (1A)
unnamed: R91.1, U20.2 (1Y)
unnamed: R92.1, U20.3 (1Z)
unnamed: R88.2, U20.7 (2A)
unnamed: R93.1, U20.6 (2Y)
unnamed: R94.1, U20.5 (2Z)
unnamed: R89.2, U20.9 (3A)
unnamed: R95.1, U20.10 (3Y)
unnamed: R96.1, U20.11 (3Z)
unnamed: R90.2, U20.15 (4A)
unnamed: R97.1, U20.14 (4Y)
unnamed: R98.1, U20.13 (4Z)
unnamed: R99.2, U23.1 (1A)
unnamed: R103.1, U23.2 (1Y)
unnamed: R104.1, U23.3 (1Z)
unnamed: R100.2, U23.7 (2A)
unnamed: R105.1, U23.6 (2Y)
unnamed: R106.1, U23.5 (2Z)
unnamed: R101.2, U23.9 (3A)
unnamed: R107.1, U23.10 (3Y)
unnamed: R108.1, U23.11 (3Z)
unnamed: R102.2, U23.15 (4A)
unnamed: R109.1, U23.14 (4Y)
unnamed: R110.1, U23.13 (4Z)
unnamed: R111.2, U26.1 (1A)
unnamed: R115.1, U26.2 (1Y)
unnamed: R116.1, U26.3 (1Z)
unnamed: R112.2, U26.7 (2A)
unnamed: R117.1, U26.6 (2Y)
unnamed: R118.1, U26.5 (2Z)
unnamed: R113.2, U26.9 (3A)
unnamed: R119.1, U26.10 (3Y)
unnamed: R120.1, U26.11 (3Z)
unnamed: R114.2, U26.15 (4A)
unnamed: R121.1, U26.14 (4Y)
unnamed: R122.1, U26.13 (4Z)
unnamed: R123.2, U29.1 (1A)
unnamed: R127.1, U29.2 (1Y)
unnamed: R128.1, U29.3 (1Z)
unnamed: R124.2, U29.7 (2A)
unnamed: R129.1, U29.6 (2Y)
unnamed: R130.1, U29.5 (2Z)
unnamed: R125.2, U29.9 (3A)
unnamed: R131.1, U29.10 (3Y)
unnamed: R132.1, U29.11 (3Z)
unnamed: R126.2, U29.15 (4A)
unnamed: R133.1, U29.14 (4Y)
unnamed: R134.1, U29.13 (4Z)
VDD: D2.1 (A1), F1.1, J9.1, J9.2
